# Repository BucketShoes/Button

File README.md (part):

# Capture button

A capture point for LARP battle games, made for [Battlecry LARP](https://battlecrylarp.org). Two teams fight
over a hand-sized button. To take it you hold its lid down for a few seconds, which is long enough
for an enemy nearby to hit you first. The button shows who owns it with a ring of team-coloured
lights, and can run a clock for each team, like a reverse chess clock: whoever owns it longest wins.

We used to mark points with scrunchies or flags on a pole, or with a chess clock, which needed a ref
standing next to it holding up a flag so players could see the score from a distance. The button lights
up for itself, and a capture takes a deliberate hold rather than the instant slap of a chess clock.

<p align="center"><a href="https://bucketshoes.github.io/Button/"><b>Open the control page</b></a>
&nbsp;·&nbsp; <a href="https://bucketshoes.github.io/Button/?demo"><b>Try the demo</b></a> (no hardware needed)</p>

The control page runs in Chrome on a phone and talks to the buttons over Bluetooth. From it a ref can see every
button at once, pause and resume the whole game, adjust clocks and change settings. The buttons work
fine without it. **The demo** runs five simulated buttons in your browser, with clocks ticking and captures happening
by themselves. Every control works on them, so open a button's settings and try things out.

| | |
|---|---|
|  |  |
| Assembled, lid on (displays off) | Board, lid and shell as delivered by JLCPCB / JLC3DP |
|  |  |
| The b43 board (KiCad) | Case section: lid, return spring and pushers over the shell |

Photos of it powered on don't come out: the displays and charge LED blow out, so the photos above show it off.

## What's in it

- **ESP32-C6** module, two 4-digit 7-segment displays (one per team), 8 WS2812 LEDs in a ring,
  three switches under the lid, a speaker, USB-C charging and an 18650 cell.
- A **3D-printed case**: a translucent lid that presses the switches through printed pushers, over a shell
  that holds the board with a twist-lock. The shell is JLC3DP's 9600 white resin, thin enough that the
  LEDs glow out through its sides. The lid is 8001 clear resin: without any smoothing treatment it's a little
  diffuse, but the large displays read easily through it.
- **Firmware** in C on ESP-IDF, with a Bluetooth LE protocol for the control page.

## What's in this repo

| Where | What |
|---|---|
| [`src/`](src) | Firmware (ESP-IDF via PlatformIO): see [Building the firmware](#building-the-firmware) |
| [`docs/index.html`](docs/index.html) | The control page, served by GitHub Pages ([`demo.js`](docs/demo.js) is its demo mode; [`sw.js`](docs/sw.js) and the manifest make it installable and usable offline) |
| [`docs/ble-protocol.md`](docs/ble-protocol.md) | The Bluetooth protocol, if you want to write your own controller |
| [`docs/hardware.md`](docs/hardware.md) | Pin map, power, displays, LEDs and audio, as built on board b43 |
| [`docs/design-notes.md`](docs/design-notes.md), [`docs/plans.md`](docs/plans.md) | Design notes, game ideas, and what's planned |
| [`pcb/`](pcb) | KiCad 10 project for board b43, and the JLC production files |
| [`case/`](case) | Case STEP (lid, shell and sleeve, v43) as sent to JLC3DP |
| [`docs/next-revision.md`](docs/next-revision.md) | **Read this before building your own:** what we'd change after the first boards and cases arrived, and the cost |

## Building one

Everything was ordered from JLC: the board assembled by JLCPCB, and the case printed in resin by JLC3DP.

- **Every assembled part has an LCSC part number** in the board file (`LCSC Part #`), so the BOM and placement files
  in [`pcb/production b43.zip`](pcb) go straight into a JLCPCB assembly order. They're mostly basic and
  promotional parts, so the extended-part fees stay low.
- **Some soldering is still needed.** JLC wouldn't place the 8 WS2812B LEDs: they're moisture class MSL 5a,
  even though they're listed as available for economic assembly. The 18650 holder on the back and any external
  wires (speaker, pedals, LED strip) are also hand-soldered.
- **A pouch cell instead of the 18650** works fine, but connect it through a plug (JBAT1 takes a 2-pin PH 2.0
  connector) rather than soldering it straight on. The ESP is always powered from the cell, so a hard-wired cell
  leaves no way to power-cycle a stuck button.
- **Order the case** from [`case/larp-v43 print.step`](case): the shell (and sleeve) in 9600 white resin, the lid in 8001 clear resin, untreated.
- **Flash the firmware** over USB-C (see below), then connect from the control page.
- **Before ordering**, read [`docs/next-revision.md`](docs/next-revision.md): the first articles showed fit,
  spring and rattle problems in the case, and a few board changes.

### Opening the board in KiCad

[`pcb/`](pcb) has the schematic, board, project libraries (`LARP.kicad_sym`, `LARP.pretty`), design rules and
Fabrication Toolkit settings. It needs KiCad 10.

- **3D models:** the EasyEDA/LCSC models aren't in the repo, because their redistribution terms are unclear. Fetch them with:

  ```
  pip install easyeda2kicad
  python tools/fetch_3d_models.py
  ```

  The script puts each model where the board expects it, and checks it against [`pcb/models.sha256`](pcb/models.sha256), the exact files
  the board was designed with. The board file and gerbers don't depend on them; only the 3D view does.
- **Schematic:** it matches the b43 board, except that USBC1 uses a different 16-pin USB-C footprint on the board.
  The mounting holes and a net tie are on the board only.
- **How the files were made:** scripts generated the KiCad files with the parts and nets but no layout. The
  layout was then done by hand in KiCad, and later tweaks were a mix of KiCad edits and direct edits to the files,
  so the files here, not the scripts, are the source.

## Licence

- **Firmware, control page and tools:** [GPL-3.0-or-later](LICENSE).
- **Hardware (`pcb/`, `case/`) and documentation:** [CC BY-SA 4.0](LICENSE-hardware.md).

## Building the firmware

The firmware is C on **ESP-IDF 5.5.1**, built with [PlatformIO](https://platformio.org) (the pioarduino platform 55.03.31,
which brings its own ESP-IDF; nothing else to install).

1. Install VS Code and its PlatformIO extension, then open this folder. The first build downloads the toolchain,
   which takes a few minutes.
2. Plug the board in by USB-C and pick its port in the status bar.
3. Run the PlatformIO **Upload** task. The ESP32-C6's native USB usually just works, but not on every module. If it won't
   connect, or keeps dropping out, power it fully down first: take out the 18650, or unplug the pouch cell. Then hold
   BOOT (inside the case) while plugging in USB, and upload. That keeps the chip in its bootloader. On USB alone the
   power peaks at startup can reset the chip in a loop, and BOOT stops the loop long enough to flash.
4. Open the control page and connect. Settings (name, mode, durations, colours and so on) are set from the page and
   saved on the button, so there's nothing to configure in the code.

From a terminal: `pio run -t upload --upload-port <port>`, then `pio device monitor --port <port>` for the serial log
(a status line every second and an event log). On Windows `pio` usually isn't on PATH; it's
`~\.platformio\penv\Scripts\pio.exe`.

Chip options are in `sdkconfig.defaults`; delete the generated `sdkconfig.button` after editing it.
The flash layout is in `partitions.csv`: a 3 MB app and a 4 MB `audio` partition.

<details>
<summary>Optional: a music clip</summary>

The `audio` partition can hold a clip of about 40 s, played from the page with the "Music clip" sound. It was added as a
speaker test, and the button works fine without it. Upload leaves it alone unless `custom_audio` in `platformio.ini` says otherwise:
`upload` also writes `audio/test_audio.bin`, and `erase` blanks it. Set it back to `keep` afterwards, because the clip makes uploads slow.

To make the clip from any MP3 (`transcode.ps1` uses Windows' own decoder, so no ffmpeg is needed):

```
powershell -File tools	ranscode.ps1 -Src "song.mp3" -OutDir <dir> -OutName music.wav
python tools\make_test_audio.py <dir>\music.wav audio	est_audio.bin
```

`make_test_audio.py` takes the first 40 s and normalises the level (see `--help` for the start point, high-pass and
compression). It also writes `audio/test_audio.wav`, the exact samples the button plays, for listening on a PC.
The format is raw 16-bit mono PCM at 48 kHz with a 16-byte header.
</details>

## Control page (Web Bluetooth)

[docs/index.html](docs/index.html) is published by GitHub Pages at
<https://bucketshoes.github.io/Button/>. Open it in Chrome (Android, or Chrome/Edge on a computer) and
press **Connect a button**. You can connect several buttons. With no hardware, add `?demo` to the address for five simulated buttons
(<https://bucketshoes.github.io/Button/?demo>).

- **Install it as an app** (optional): use the **Install as an app** link at the bottom of the page, or Chrome's menu
  (**Add to Home screen** on Android, **Install** on a computer). The page doesn't pop up an install offer by itself.
  It then opens full-screen from its own icon. Installed or not, it also works with no internet once it has been opened
  once, which helps at game sites with no reception. With a connection it always loads the newest version.
- **iPhone:** no iPhone browser has Web Bluetooth (they're all Safari underneath, including Chrome), so the page
  can't connect, installed or not. A Web Bluetooth browser app such as Bluefy may work; it hasn't been tested.

- **Keep screen on** (at the bottom of the page, on by default): stops the phone locking while the page is in front, so a ref can glance at it mid-game. Chrome allows it straight away; a browser that wants a tap first gets one from the next tap anywhere on the page. Next to it, "(on)" means it is working. Untick it to save battery; the choice is remembered.
- **Game bar** (top): pause and resume the whole game, and play a sound (whistle by default) on every button. Game resume undoes the game pause: each button goes back to exactly what it was doing, so a button that was paused or uncaptured stays that way.
- **Overview:** one row per button, sized so about 5 fit on a phone screen. Name and battery on the left, then a box per team (team names once at the top of each column):
  - thick border in the team colour, filled for the owner;
  - underlined time while that clock is ticking, blinking on a win. In one-timer mode the shared clock shows in the owner's box only, and the other box is empty;
  - a small pie fills while someone holds the lid, in the box of the team about to capture;
  - tap a row to jump to that button's panel.
- **Each button** gets its own panel below:

- **Controls:** start, pause, reset, identify (displays and ring flash with beeps for 3 s), battery, and power off.
- **Owner:** set the owner (uncaptured / team 1 / team 2).
- **Reboot** (in settings), for when something is stuck. Settings are kept; the game state is lost.
- **Sounds:** play any of the button's sounds, or stop them.
- **Clocks:** live clocks (one shared clock in one-timer mode), −1 min / −10 s, +1 min / +10 s, or set an exact time (m:ss), even while running.
- **Settings (saved on the button):**
  - name and mode (teams only / one timer / two timers);
  - count down or up, and whether the numbers show on the displays;
  - durations (one in one-timer mode), the owner after reset, the first capture (random / team 1 / team 2), the hold time, the team colours, the volume and the LED brightness;
  - "Copy to all" sends the settings to every connected button, keeping each name.
- **More for all buttons** (under the overview): identify, power on and power off all of them at once.
- **Reboots:** the panel shows how many times the button restarted since power-on, why it last did (for example brown-out) and how long ago. Wakes from deep sleep (shipping, low battery) don't count. The count is kept in RTC RAM: a reset, a reflash or a brown-out keeps it; only losing all power (the cell and USB both gone) clears it.
- **Wall clock** with seconds in the top corner.

The protocol is in [docs/ble-protocol.md](docs/ble-protocol.md).

## Behaviour

- **Modes:**
  - **Teams only:** the ring shows who owns the button. There are no clocks: the owner's display shows dashes ("--:--") with the same colon, highlight and hold cues as a clock, and the other display is blank.
  - **One timer:** one shared clock, which runs whichever team owns the button. Whoever owns it when the clock runs out wins. It shows only on the owner's display, and the other display is blank, so it reads as one clock that belongs to them. While uncaptured it shows on one display only, neither lit: the team the next press goes for (the first display when that's random).
  - **Two timers:** a reverse chess clock; the owner's clock runs.
  - **"Own" and "hold":** a team *owns* the button (it's in their control); a player *holds* the lid (pressing it).
- **Clocks:** count down (win at 0:00) or up (win at the duration; a duration of 0 means no limit). Default: two timers counting down from 10:00.
- **Face press:** any of the three switches counts (an OR). The lid counts as pressed until 50 ms after the last contact.
- **Hold**, where H is the hold time (default 3 s):
  - **Up to H:** the ring shows the team about to capture. The first LED is lit at once, and the others wait dim, at the lowest brightness setting. Each comes on in turn with a short smooth fade (0.2 s) at the end of its fifth of the hold, so it's a clear step around the ring, and the capture happens as the 6th comes on. While it builds, the lit LEDs are at least 16 % (8 times the dim ones, so they're clearly apart at any setting) and the team LEDs light as bright as the ring; it goes back to the set brightness once captured. The build-up sound is made for the hold time, so it lasts exactly until the capture: a rising whoop (sci-fi), or drums accelerating under a climbing horn, ending in a snare roll (medieval). Letting go early puts it back as it was.
  - **At H, capture:** while running it goes to the other team; while paused it resumes with the same team. The ring and displays go dark for 0.1 s, as a "done", then show the new owner as normal while its call plays out. The count towards the pause starts only once the call has finished, at C (H plus the longer of the two teams' calls, so it's the same whichever team captured: about 0.65 s in sci-fi, 1.5 s in medieval), so the call isn't talked over and the next thing is clearly something else.
  - **Uncaptured:** the team is decided the moment the hold starts and shows straight away: the ring fills in its colour and its display lights. Wrong colour? Let go and press again: every press that doesn't capture flips the team for the next press. The first press uses the "first capture" setting, which is random by default.
  - **C to C+4 s:** the ring fills white with a ding each second, then a **pause** at C+4 s (about 8 s with the default hold). The clocks go back to where they were before the hold, and the paused owner is:
    - **was running:** whoever had it before the hold;
    - **was uncaptured:** the team just picked, so a hold to the pause pre-sets the owner at 10:00 (for example at a respawn);
    - **was paused:** the same team: the hold is undone.
  - **C+4 to C+9 s:** doom each second, then a **reset** at C+9 s (about 13 s).
  - **C+9 to C+14 s:** after a second, the displays say "HoLd" "oFF" with a falling tone and the ring drains; at C+14 s (about 18 s) it **powers off**. Let go before that and it stays on, just reset.
  - **During a game pause** (from the page): a press plays the pause sound and nothing is captured, so a player who hasn't noticed can't change anything. The ring fills slowly white; at H+4 s the button leaves the game pause into a regular pause, owner and clocks unchanged, and works normally from then on (so the page is never required). H+9 s still resets. (Nothing is captured, so there is no call to wait for: C is H here, and after a win.)
  - **After a win**, the fanfare repeats for 20 s. Holding dings every second all the way to the reset (there is no pause to warn about): H silences the fanfare, and H+9 s resets.
- **Idle cues:**
  - **Not held, the button shows only the true state.** A hold let go early snaps straight back, so nobody runs off thinking they captured it.
  - **Uncaptured:** a faint white pulse on the ring (0–10 %, 0.5 Hz), no team colour, and neither display highlighted. The team the next press goes for has one colon dot missing: subtle, for admins.
  - **Paused with an owner:** the ring blinks faintly in their colour, and their display shows a single slow-blinking dot instead of the colon.
- **After reset:** uncaptured, or owned by the team set in "after reset". In teams-only mode that team is simply live. With clocks it waits, paused, for Start or a hold.
- **Lines** (tug-of-war, forge-a-path; set up in the page's "Lines" (changes go to the buttons on Save), or by holding several buttons to the reset at once; default settings take a button out of its line):
  - A team can take a button only next to one it owns, or at its end of the line (each end's team, or none, is a setting). Forge-a-path: a button once taken stays taken.
  - Retake (a button just taken can't be taken back) and advance (a button just opened by its neighbour's capture can't be taken yet) are 0 s and 20 s by default (0 is allowed for either), counted on the network clock. An owner an admin sets is open at once (no count); saving a line's settings keeps any count that's running. A press on a paused button goes to its own owner, a resume, which is always allowed.
  - **Displays:** nobody can take it: "--:--" on both, dim. Counting down to when a team can: the time on that team's display, the rest as a teams-only button. Once it can be taken it's simply a teams-only button.
  - **Sounds:** a neighbour's capture that opens this button, or starts its count, plays a brief alert here ("dun dun" and a horn, or two beeps in sci-fi); the count running out plays a bell (or a blip).
  - **A press that isn't allowed:** a short low "no" and a red flash, and nothing builds up or captures. Not next to theirs: "nEEd" and the number of the button to take first, for 2 s. Holding on still pauses and resets as usual.
  - **Forming without the page:** hold several buttons at once (a stack, pressed together) until the reset. From the pause on they flash one shared colour together; at the reset they become a line, numbered in node-id order, the first half team 1, the rest team 2 (a middle one either), and show "LinE" and their place ("4  3": line 4, 3rd; lines are numbered 1–6, each with its own colour, and a new one avoids the numbers in use) for 20 s, with a sweep down the line in its colour. A button held to the reset alone leaves its line. A reset in a line goes back to the team the line gave it; the button's own "after reset" setting is kept for when it leaves. The line is kept in flash, so a button that restarts is still in it. In a line a button is in teams-only mode; leaving puts its own mode back.
  - **Four taps:** "LinE" and its place again for 2 s ("--" when not in a line); on joining it shows for 15 s.
- **Triple tap:** battery ("bAtt" plus a percent for 2 s, with a green gauge on the ring). It works in every mode and with the numbers hidden. The latest tap code is what shows; 1, 2 or 5 or more taps put the display back to normal.
- **Power:** see "Power" below.
- **BOOT:**
  - Hold: the displays say "HoLd" "oFF" with a falling tone, and at 3 s it **powers off** (no need to let go).
  - Keep holding to 8 s: restore the default settings (it wakes briefly to play the sound).
  - A press while the music clip plays only stops the clip.
- **Volume** defaults to 80 % and **LEDs** to 50 %. Volume is in even dB steps (0.4 dB a percent, 100 % = full scale) and goes on to 125 % (+10 dB): past 100 the loudest peaks go into a soft knee above −2 dBFS. Full volume can brown out on USB-only power. The brightness setting dims the displays too. In the medieval set the plain beeps (admin sounds) play 6 dB lower, to sit with the instruments.
- **Brown-out recovery:**
  - The game carries on. The game state is copied to RTC RAM all the time, and a brown-out reset leaves that RAM and the low-power timer running. After a brown-out, crash or watchdog reset, the button comes back with the same owner, clocks and running/paused state, with the clock advanced by the second or so it spent rebooting. A button that was off comes back off. If the RAM didn't survive (the checksum fails), or the power was really lost, it starts fresh as after a reset. A reboot from the page also starts fresh.
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
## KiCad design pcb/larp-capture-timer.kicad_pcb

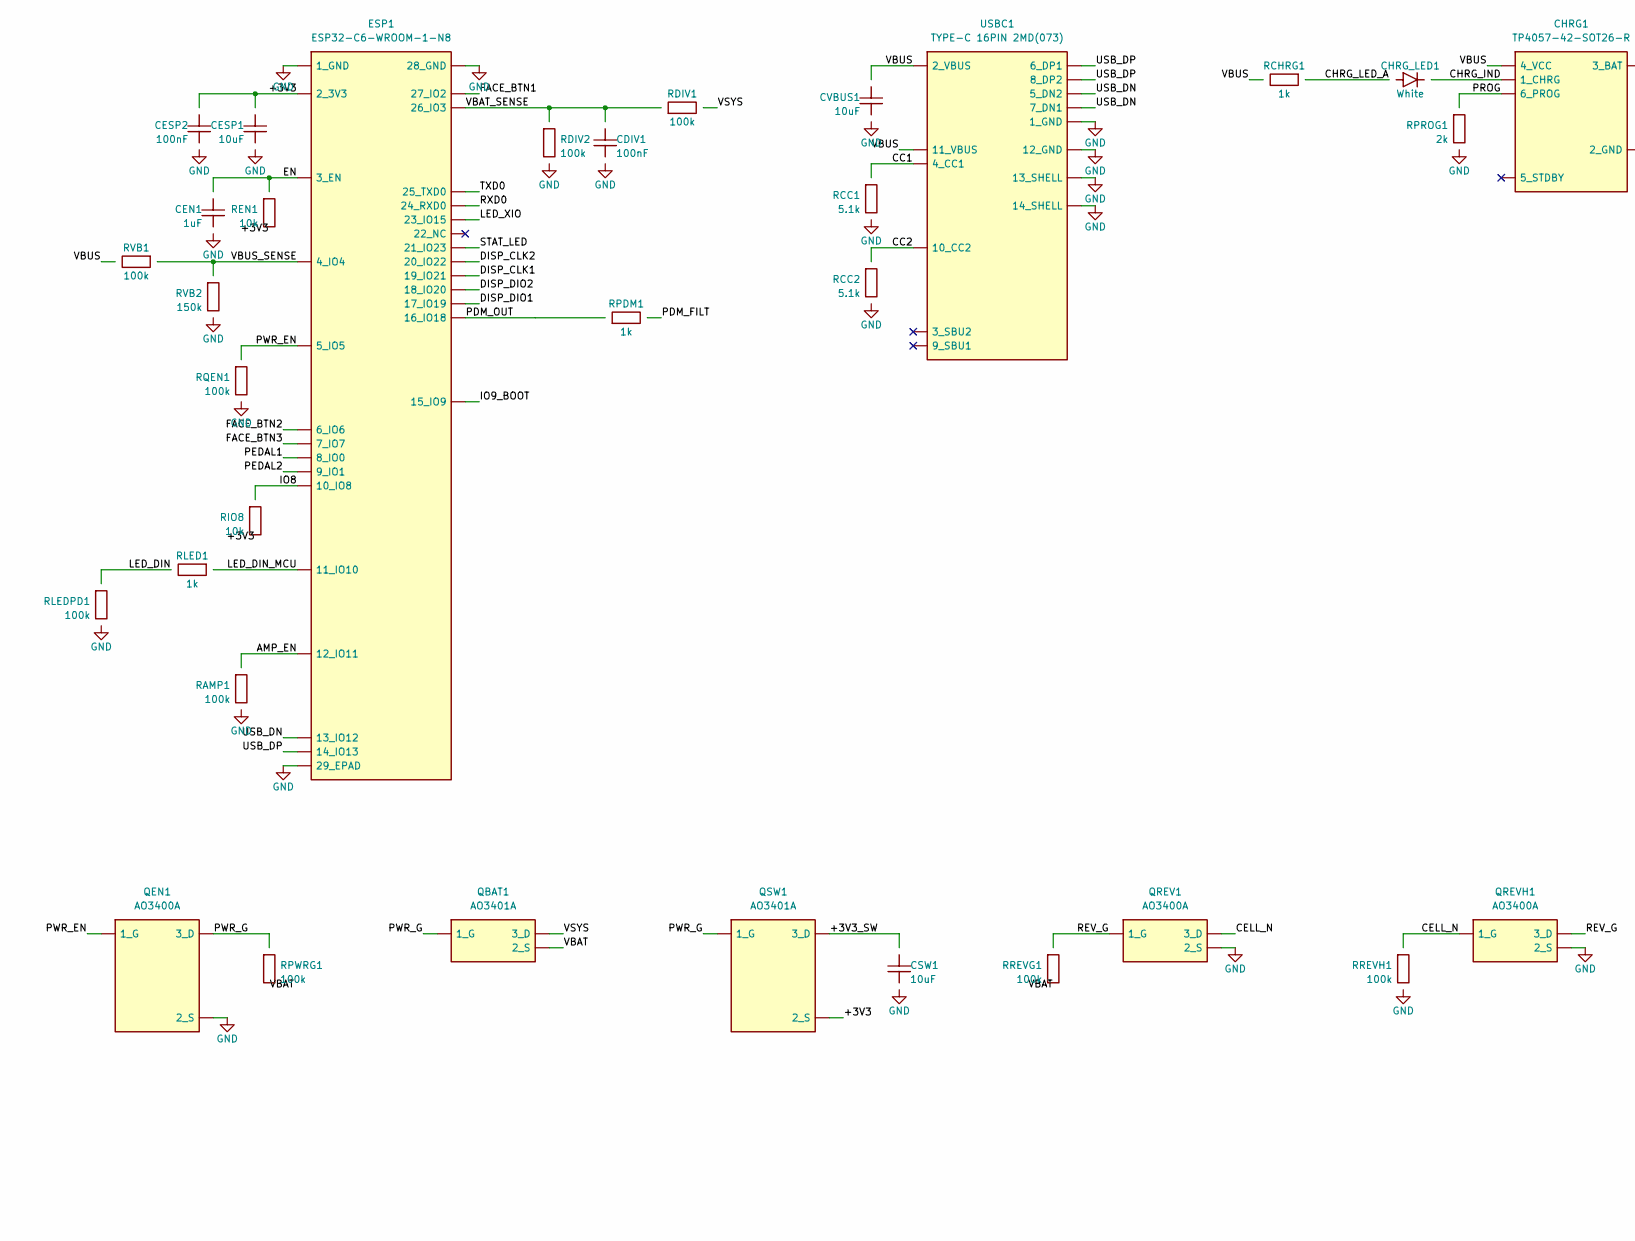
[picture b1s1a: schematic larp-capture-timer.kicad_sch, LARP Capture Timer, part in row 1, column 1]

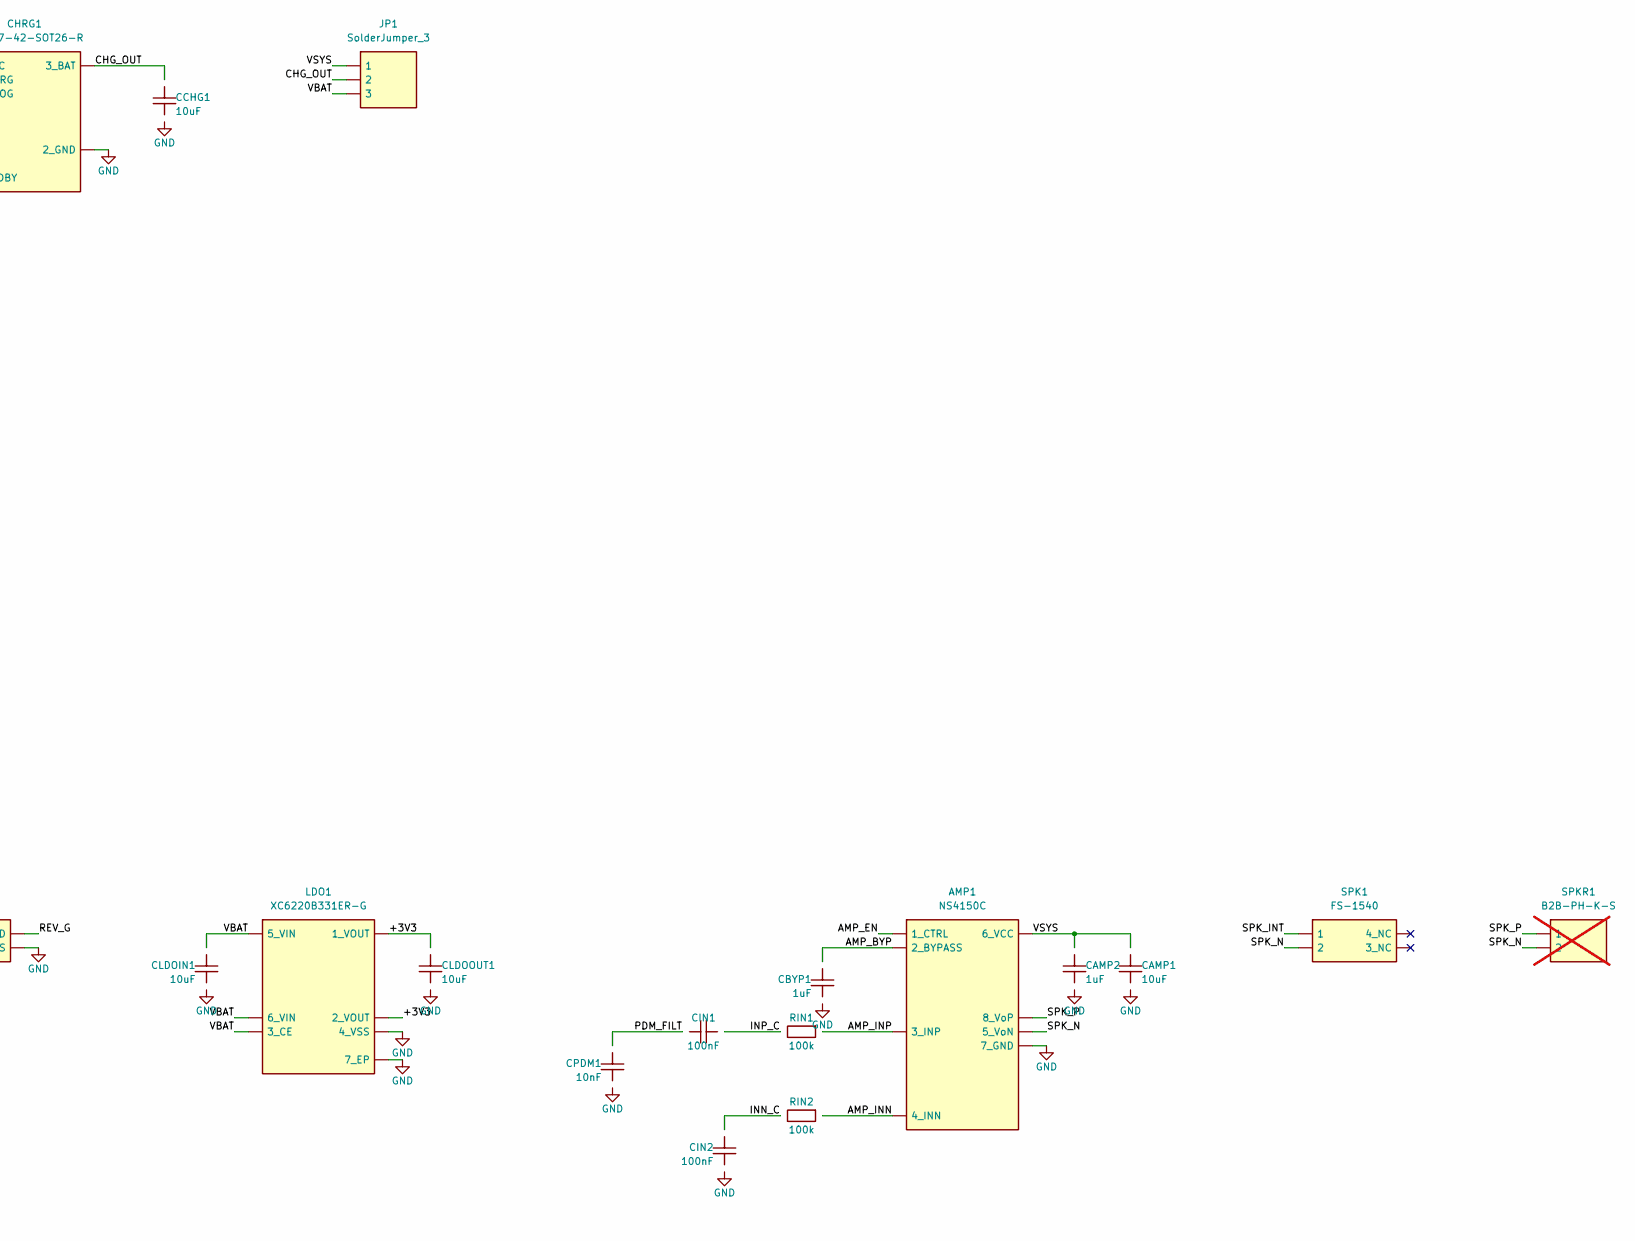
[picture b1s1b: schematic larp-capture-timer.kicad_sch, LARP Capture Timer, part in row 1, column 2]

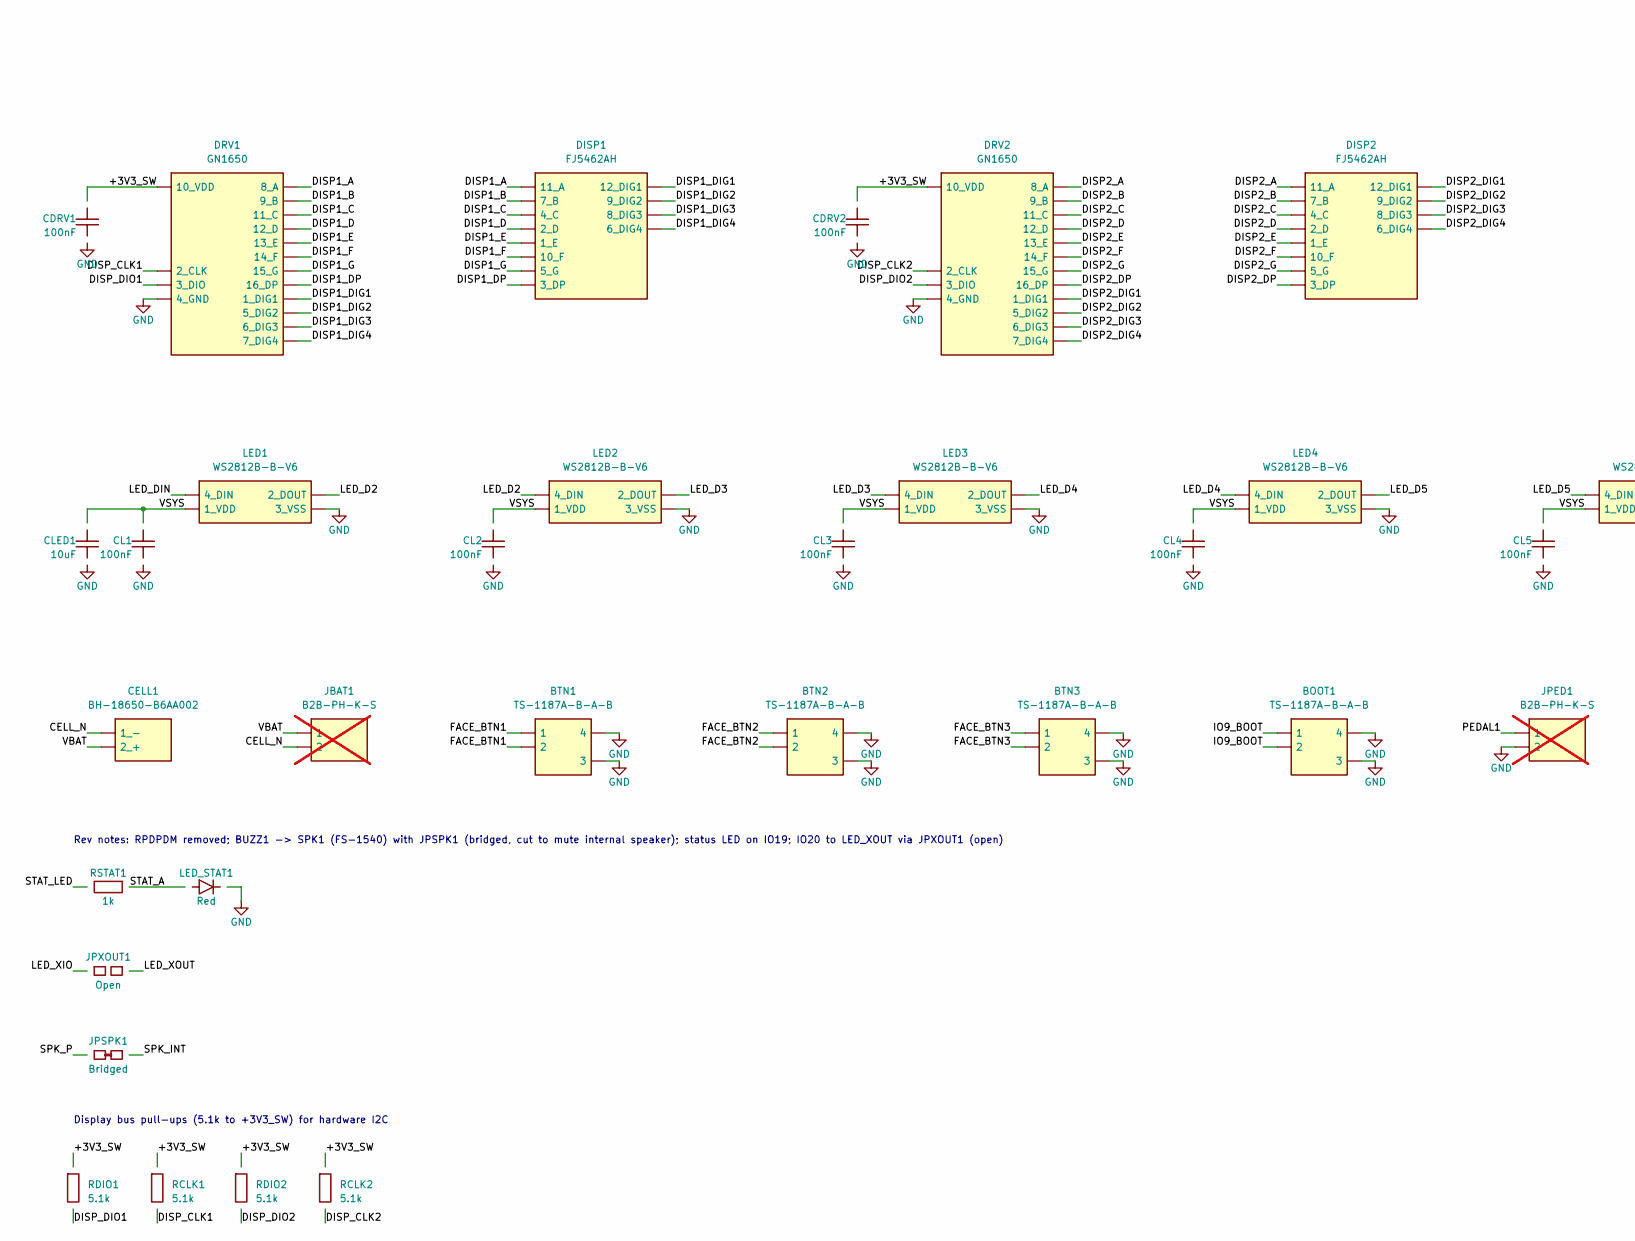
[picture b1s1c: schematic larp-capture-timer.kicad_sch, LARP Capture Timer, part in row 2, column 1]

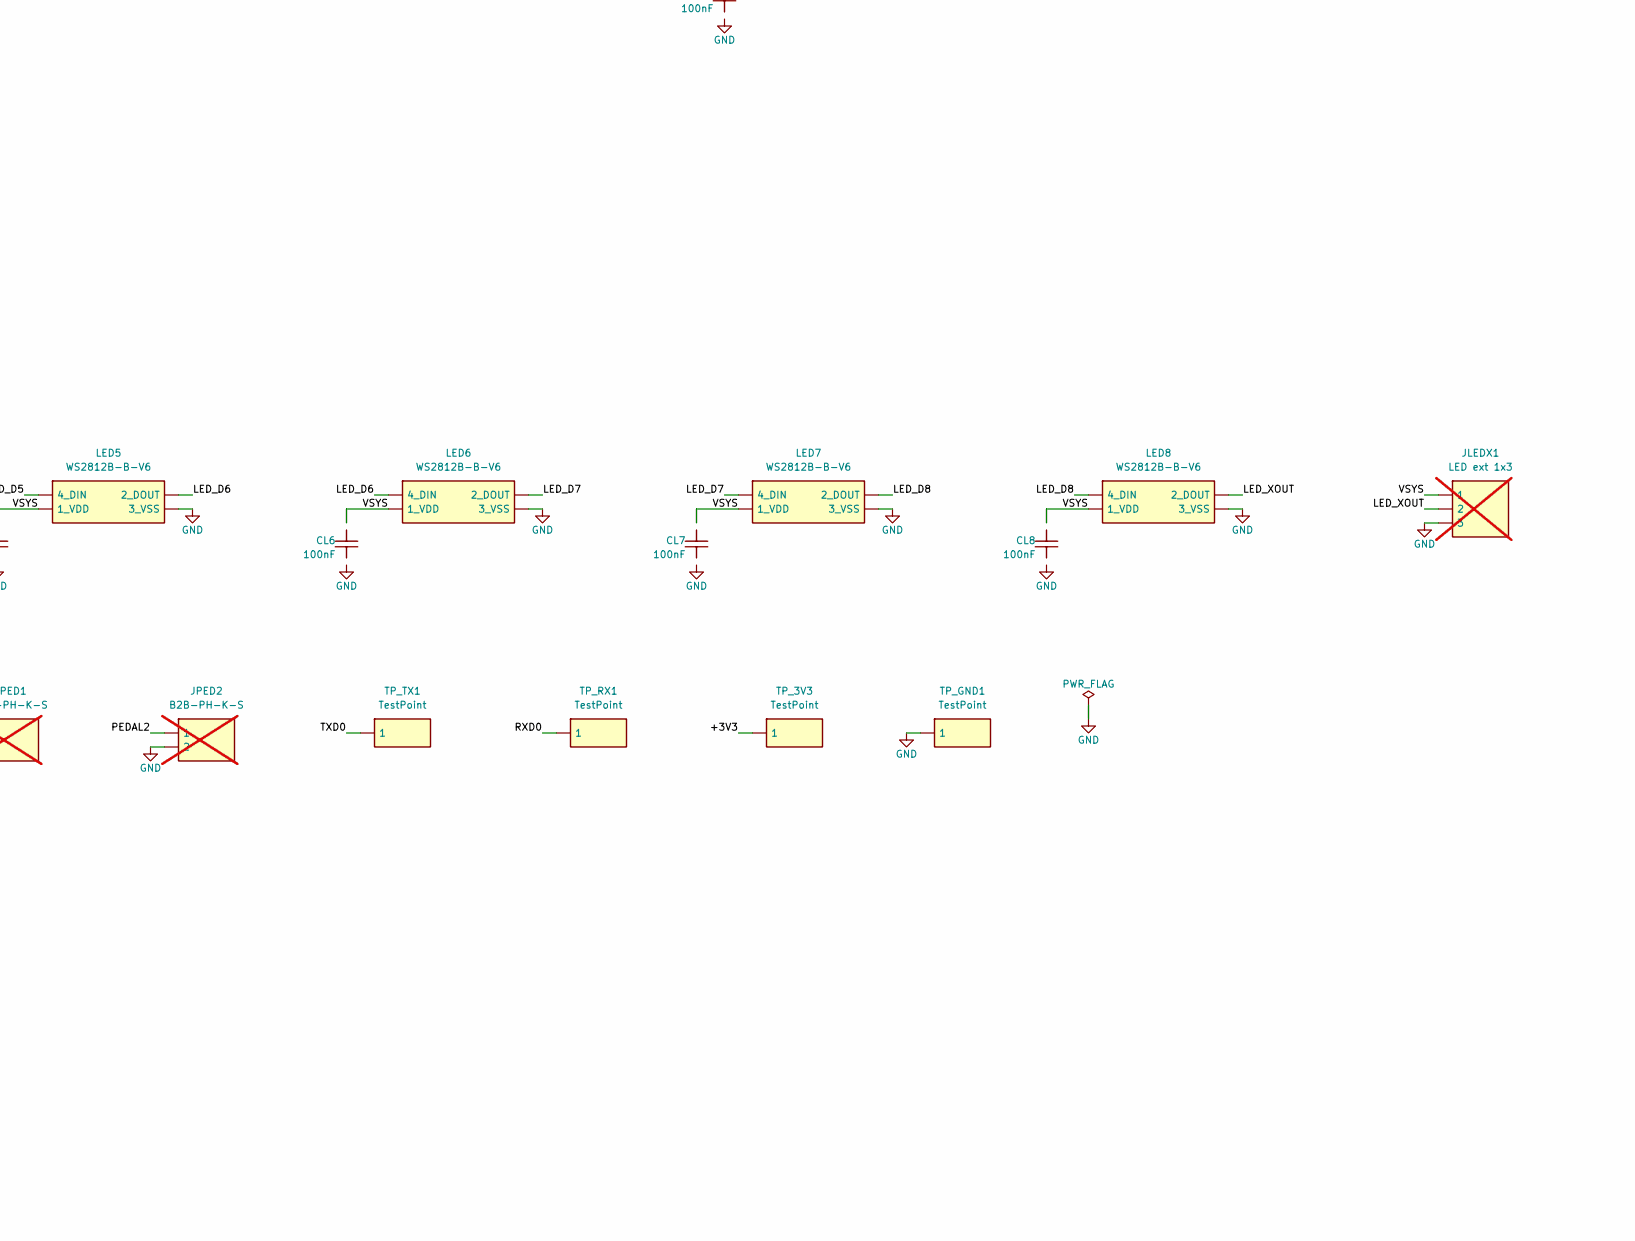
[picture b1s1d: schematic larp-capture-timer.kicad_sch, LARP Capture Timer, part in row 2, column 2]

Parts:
AMP1: NS4150C; SOP-8_L4.9-W3.9-P1.27-LS6.0-BL_NS4150C; LCSC Part # C2875838
BOOT1: TS-1187A-B-A-B; SW-SMD_4P-L5.1-W5.1-P3.70-LS6.5-TL_H1.5; LCSC Part # C318884
BTN1, BTN2, BTN3: TS-1187A-B-A-B; SW-SMD_4P-L5.1-W5.1-P3.70-LS6.5-TL_H1.5; LCSC Part # C318884
CAMP1: 10uF; C_0603_1608Metric; LCSC Part # C19702
CAMP2: 1uF; C_0603_1608Metric; LCSC Part # C15849
CBYP1: 1uF; C_0603_1608Metric; LCSC Part # C15849
CCHG1: 10uF; C_0603_1608Metric; LCSC Part # C19702
CDIV1: 100nF; C_0603_1608Metric; LCSC Part # C14663
CDRV1, CDRV2: 100nF; C_0603_1608Metric; LCSC Part # C14663
CELL1: BH-18650-B6AA002; BATTERY-SMD_18650-1S-L77.1-W20.7-1; LCSC Part # C7525438
CEN1: 1uF; C_0603_1608Metric; LCSC Part # C15849
CESP1: 10uF; C_0603_1608Metric; LCSC Part # C19702
CESP2: 100nF; C_0603_1608Metric; LCSC Part # C14663
CHRG1: TP4057-42-SOT26-R; SOT-23-6_L2.9-W1.6-P0.95-LS2.8-BL_TP4057-42-SOT26-R; LCSC Part # C12044
CHRG_LED1: White; LED_0603_KA; LCSC Part # C2290
CIN1, CIN2: 100nF; C_0603_1608Metric; LCSC Part # C14663
CL1, CL2, CL3, CL4, CL5, CL6, CL7, CL8: 100nF; C_0603_1608Metric; LCSC Part # C14663
CLDOIN1: 10uF; C_0603_1608Metric; LCSC Part # C19702
CLDOOUT1: 10uF; C_0603_1608Metric; LCSC Part # C19702
CLED1: 10uF; C_0603_1608Metric; LCSC Part # C19702
CPDM1: 10nF; C_0603_1608Metric; LCSC Part # C57112
CSW1: 10uF; C_0603_1608Metric; LCSC Part # C19702
CVBUS1: 10uF; C_0603_1608Metric; LCSC Part # C19702
DISP1, DISP2: FJ5462AH; LED-SEG-TH_12P-L50.3-W19.0-P2.54-S15.24-BL_FJ5462AH; LCSC Part # C46908
DRV1, DRV2: GN1650; SOP-16_L9.9-W3.9-P1.27-LS6.1-BL_GN1650; LCSC Part # C427456
ESP1: ESP32-C6-WROOM-1-N8; ESP32-C6-WROOM-1; LCSC Part # C5366877
JBAT1: B2B-PH-K-S; CONN-TH_B2B-PH-K-S; LCSC Part # C131337; not fitted
JLEDX1: LED ext 1x3; HDR-TH_3P-P2.54-V-M_PZ254V-11-03P; LCSC Part # C2937625; not fitted
JP1: SolderJumper_3; SolderJumper-3_P1.3mm_Open_Pad1.0x1.5mm
JPED1, JPED2: B2B-PH-K-S; CONN-TH_B2B-PH-K-S; LCSC Part # C131337; not fitted
JPSPK1: Bridged; SolderJumper-2_P1.3mm_Bridged_RoundedPad1.0x1.5mm
JPXOUT1: Open; SolderJumper-2_P1.3mm_Open_RoundedPad1.0x1.5mm
LDO1: XC6220B331ER-G; USP-6C_L2.0-W1.8-P0.50-BL-EP_XC6220B331ER-G; LCSC Part # C3013657
LED1, LED2, LED3, LED4, LED5, LED6, LED7, LED8: WS2812B-B-V6; LED-SMD_4P-L5.0-W5.0-TL_WS2812B-B_WS2812B-B-V6; LCSC Part # C52941391
LED_STAT1: Red; LED_0603_KA; LCSC Part # C2286
QBAT1: AO3401A; SOT-23_L2.9-W1.3-P1.90-LS2.4-BR_AO3401A; LCSC Part # C15127
QEN1: AO3400A; SOT-23-3_L2.9-W1.3-P1.90-LS2.4-BR_AO3400A; LCSC Part # C20917
QREV1: AO3400A; SOT-23-3_L2.9-W1.3-P1.90-LS2.4-BR_AO3400A; LCSC Part # C20917
QREVH1: AO3400A; SOT-23-3_L2.9-W1.3-P1.90-LS2.4-BR_AO3400A; LCSC Part # C20917
QSW1: AO3401A; SOT-23_L2.9-W1.3-P1.90-LS2.4-BR_AO3401A; LCSC Part # C15127
RAMP1: 100k; R_0603_1608Metric; LCSC Part # C25803
RCC1, RCC2: 5.1k; R_0603_1608Metric; LCSC Part # C23186
RCHRG1: 1k; R_0603_1608Metric; LCSC Part # C21190
RCLK1, RCLK2: 5.1k; R_0603_1608Metric; LCSC Part # C23186
RDIO1, RDIO2: 5.1k; R_0603_1608Metric; LCSC Part # C23186
RDIV1, RDIV2: 100k; R_0603_1608Metric; LCSC Part # C25803
REN1: 10k; R_0603_1608Metric; LCSC Part # C25804
RIN1, RIN2: 100k; R_0603_1608Metric; LCSC Part # C25803
RIO8: 10k; R_0603_1608Metric; LCSC Part # C25804
RLED1: 1k; R_0603_1608Metric; LCSC Part # C21190
RLEDPD1: 100k; R_0603_1608Metric; LCSC Part # C25803
RPDM1: 1k; R_0603_1608Metric; LCSC Part # C21190
RPROG1: 2k; R_0603_1608Metric; LCSC Part # C22975
RPWRG1: 100k; R_0603_1608Metric; LCSC Part # C25803
RQEN1: 100k; R_0603_1608Metric; LCSC Part # C25803
RREVG1: 100k; R_0603_1608Metric; LCSC Part # C25803
RREVH1: 100k; R_0603_1608Metric; LCSC Part # C25803
RSTAT1: 1k; R_0603_1608Metric; LCSC Part # C21190
RVB1: 100k; R_0603_1608Metric; LCSC Part # C25803
RVB2: 150k; R_0603_1608Metric; LCSC Part # C22807
SPK1: FS-1540; SPK-SMD_FS-1540; LCSC Part # C482341
SPKR1: B2B-PH-K-S; CONN-TH_B2B-PH-K-S; LCSC Part # C131337; not fitted
TP_3V3: TestPoint; TestPoint_Pad_D1.0mm
TP_GND1: TestPoint; TestPoint_Pad_D1.0mm
TP_RX1: TestPoint; TestPoint_Pad_D1.0mm
TP_TX1: TestPoint; TestPoint_Pad_D1.0mm
USBC1: TYPE-C 16PIN 2MD(073); USB-C-SMD_TYPE-C-16PIN-2MD-073_TYPE-C16PIN2MD073; LCSC Part # C2765186

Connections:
/+3V3: CESP1.1, CESP2.1, CLDOOUT1.1, ESP1.2_3V3, LDO1.1_VOUT, LDO1.2_VOUT, QSW1.2_S, REN1.2, RIO8.2, TP_3V3.1 (1_1)
/+3V3_SW: CDRV1.1, CDRV2.1, CSW1.1, DRV1.10_VDD, DRV2.10_VDD, QSW1.3_D, RCLK1.1, RCLK2.1, RDIO1.1, RDIO2.1
/AMP_BYP: AMP1.2_BYPASS, CBYP1.1
/AMP_EN: AMP1.1_CTRL, ESP1.12_IO11, RAMP1.1
/AMP_INN: AMP1.4_INN, RIN2.1
/AMP_INP: AMP1.3_INP, RIN1.1
/CC1: RCC1.1, USBC1.4_CC1
/CC2: RCC2.1, USBC1.10_CC2
/CELL_N: CELL1.1_-, JBAT1.2, QREV1.3_D, QREVH1.1_G, RREVH1.1
/CHG_OUT: CCHG1.1, CHRG1.3_BAT, JP1.2
/CHRG_IND: CHRG1.1_CHRG, CHRG_LED1.1_K
/CHRG_LED_A: CHRG_LED1.2_A, RCHRG1.1
/DISP1_A: DISP1.11_A, DRV1.8_A
/DISP1_B: DISP1.7_B, DRV1.9_B
/DISP1_C: DISP1.4_C, DRV1.11_C
/DISP1_D: DISP1.2_D, DRV1.12_D
/DISP1_DIG1: DISP1.12_DIG1, DRV1.1_DIG1
/DISP1_DIG2: DISP1.9_DIG2, DRV1.5_DIG2
/DISP1_DIG3: DISP1.8_DIG3, DRV1.6_DIG3
/DISP1_DIG4: DISP1.6_DIG4, DRV1.7_DIG4
/DISP1_DP: DISP1.3_DP, DRV1.16_DP
/DISP1_E: DISP1.1_E, DRV1.13_E
/DISP1_F: DISP1.10_F, DRV1.14_F
/DISP1_G: DISP1.5_G, DRV1.15_G
/DISP2_A: DISP2.11_A, DRV2.8_A
/DISP2_B: DISP2.7_B, DRV2.9_B
/DISP2_C: DISP2.4_C, DRV2.11_C
/DISP2_D: DISP2.2_D, DRV2.12_D
/DISP2_DIG1: DISP2.12_DIG1, DRV2.1_DIG1
/DISP2_DIG2: DISP2.9_DIG2, DRV2.5_DIG2
/DISP2_DIG3: DISP2.8_DIG3, DRV2.6_DIG3
/DISP2_DIG4: DISP2.6_DIG4, DRV2.7_DIG4
/DISP2_DP: DISP2.3_DP, DRV2.16_DP
/DISP2_E: DISP2.1_E, DRV2.13_E
/DISP2_F: DISP2.10_F, DRV2.14_F
/DISP2_G: DISP2.5_G, DRV2.15_G
/DISP_CLK1: DRV1.2_CLK, ESP1.19_IO21, RCLK1.2
/DISP_CLK2: DRV2.2_CLK, ESP1.20_IO22, RCLK2.2
/DISP_DIO1: DRV1.3_DIO, ESP1.17_IO19, RDIO1.2
/DISP_DIO2: DRV2.3_DIO, ESP1.18_IO20, RDIO2.2
/EN: CEN1.1, ESP1.3_EN, REN1.1
/FACE_BTN1: BTN1.1, BTN1.2, ESP1.27_IO2
/FACE_BTN2: BTN2.1, BTN2.2, ESP1.6_IO6
/FACE_BTN3: BTN3.1, BTN3.2, ESP1.7_IO7
/INN_C: CIN2.1, RIN2.2
/INP_C: CIN1.1, RIN1.2
/IO8: ESP1.10_IO8, RIO8.1
/IO9_BOOT: BOOT1.1, BOOT1.2, ESP1.15_IO9
/LED_D2: LED1.2_DOUT, LED2.4_DIN
/LED_D3: LED2.2_DOUT, LED3.4_DIN
/LED_D4: LED3.2_DOUT, LED4.4_DIN
/LED_D5: LED4.2_DOUT, LED5.4_DIN
/LED_D6: LED5.2_DOUT, LED6.4_DIN
/LED_D7: LED6.2_DOUT, LED7.4_DIN
/LED_D8: LED7.2_DOUT, LED8.4_DIN
/LED_DIN: LED1.4_DIN, RLED1.2, RLEDPD1.1
/LED_DIN_MCU: ESP1.11_IO10, RLED1.1
/LED_XIO: ESP1.23_IO15, JPXOUT1.2
/LED_XOUT: JLEDX1.2, JPXOUT1.1, LED8.2_DOUT
/PDM_FILT: CIN1.2, CPDM1.1, RPDM1.2
/PDM_OUT: ESP1.16_IO18, RPDM1.1
/PEDAL1: ESP1.8_IO0, JPED1.1
/PEDAL2: ESP1.9_IO1, JPED2.1
/PROG: CHRG1.6_PROG, RPROG1.1
/PWR_EN: ESP1.5_IO5, QEN1.1_G, RQEN1.1
/PWR_G: QBAT1.1_G, QEN1.3_D, QSW1.1_G, RPWRG1.1
/REV_G: QREV1.1_G, QREVH1.3_D, RREVG1.1
/RXD0: ESP1.24_RXD0, TP_RX1.1 (1_1)
/SPK_INT: JPSPK1.1, SPK1.1
/SPK_N: AMP1.5_VoN, SPK1.2, SPKR1.2
/SPK_P: AMP1.8_VoP, JPSPK1.2, SPKR1.1
/STAT_A: LED_STAT1.2_A, RSTAT1.1
/STAT_LED: ESP1.21_IO23, RSTAT1.2
/TXD0: ESP1.25_TXD0, TP_TX1.1 (1_1)
/USB_DN: ESP1.13_IO12, USBC1.5_DN2, USBC1.7_DN1
/USB_DP: ESP1.14_IO13, USBC1.6_DP1, USBC1.8_DP2
/VBAT: CELL1.2_+, CLDOIN1.1, JBAT1.1, JP1.3, LDO1.3_CE, LDO1.5_VIN, LDO1.6_VIN, QBAT1.2_S, RPWRG1.2, RREVG1.2
/VBAT_SENSE: CDIV1.1, ESP1.26_IO3, RDIV1.1, RDIV2.1
/VBUS: CHRG1.4_VCC, CVBUS1.1, RCHRG1.2, RVB1.2, USBC1.2_VBUS, USBC1.11_VBUS
/VBUS_SENSE: ESP1.4_IO4, RVB1.1, RVB2.1
/VSYS: AMP1.6_VCC, CAMP1.1, CAMP2.1, CL1.1, CL2.1, CL3.1, CL4.1, CL5.1, CL6.1, CL7.1, CL8.1, CLED1.1, JLEDX1.1, JP1.1, LED1.1_VDD, LED2.1_VDD, LED3.1_VDD, LED4.1_VDD, LED5.1_VDD, LED6.1_VDD, LED7.1_VDD, LED8.1_VDD, QBAT1.3_D, RDIV1.2
GND: AMP1.7_GND, BOOT1.3, BOOT1.4, BTN1.3, BTN1.4, BTN2.3, BTN2.4, BTN3.3, BTN3.4, CAMP1.2, CAMP2.2, CBYP1.2, CCHG1.2, CDIV1.2, CDRV1.2, CDRV2.2, CEN1.2, CESP1.2, CESP2.2, CHRG1.2_GND, CIN2.2, CL1.2, CL2.2, CL3.2, CL4.2, CL5.2, CL6.2, CL7.2, CL8.2, CLDOIN1.2, CLDOOUT1.2, CLED1.2, CPDM1.2, CSW1.2, CVBUS1.2, DRV1.4_GND, DRV2.4_GND, ESP1.1_GND, ESP1.28_GND, ESP1.29_EPAD, JLEDX1.3, JPED1.2, JPED2.2, LDO1.4_VSS, LDO1.7_EP, LED1.3_VSS, LED2.3_VSS, LED3.3_VSS, LED4.3_VSS, LED5.3_VSS, LED6.3_VSS, LED7.3_VSS, LED8.3_VSS, LED_STAT1.1_K, QEN1.2_S, QREV1.2_S, QREVH1.2_S, RAMP1.2, RCC1.2, RCC2.2, RDIV2.2, RLEDPD1.2, RPROG1.2, RQEN1.2, RREVH1.2, RVB2.2, TP_GND1.1 (1_1), USBC1.1_GND, USBC1.12_GND, USBC1.13_SHELL, USBC1.14_SHELL

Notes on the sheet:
Rev notes: RPDPDM removed; BUZZ1 -> SPK1 (FS-1540) with JPSPK1 (bridged, cut to mute internal speaker); status LED on IO19; IO20 to LED_XOUT via JPXOUT1 (open)
Display bus pull-ups (5.1k to +3V3_SW) for hardware I2C

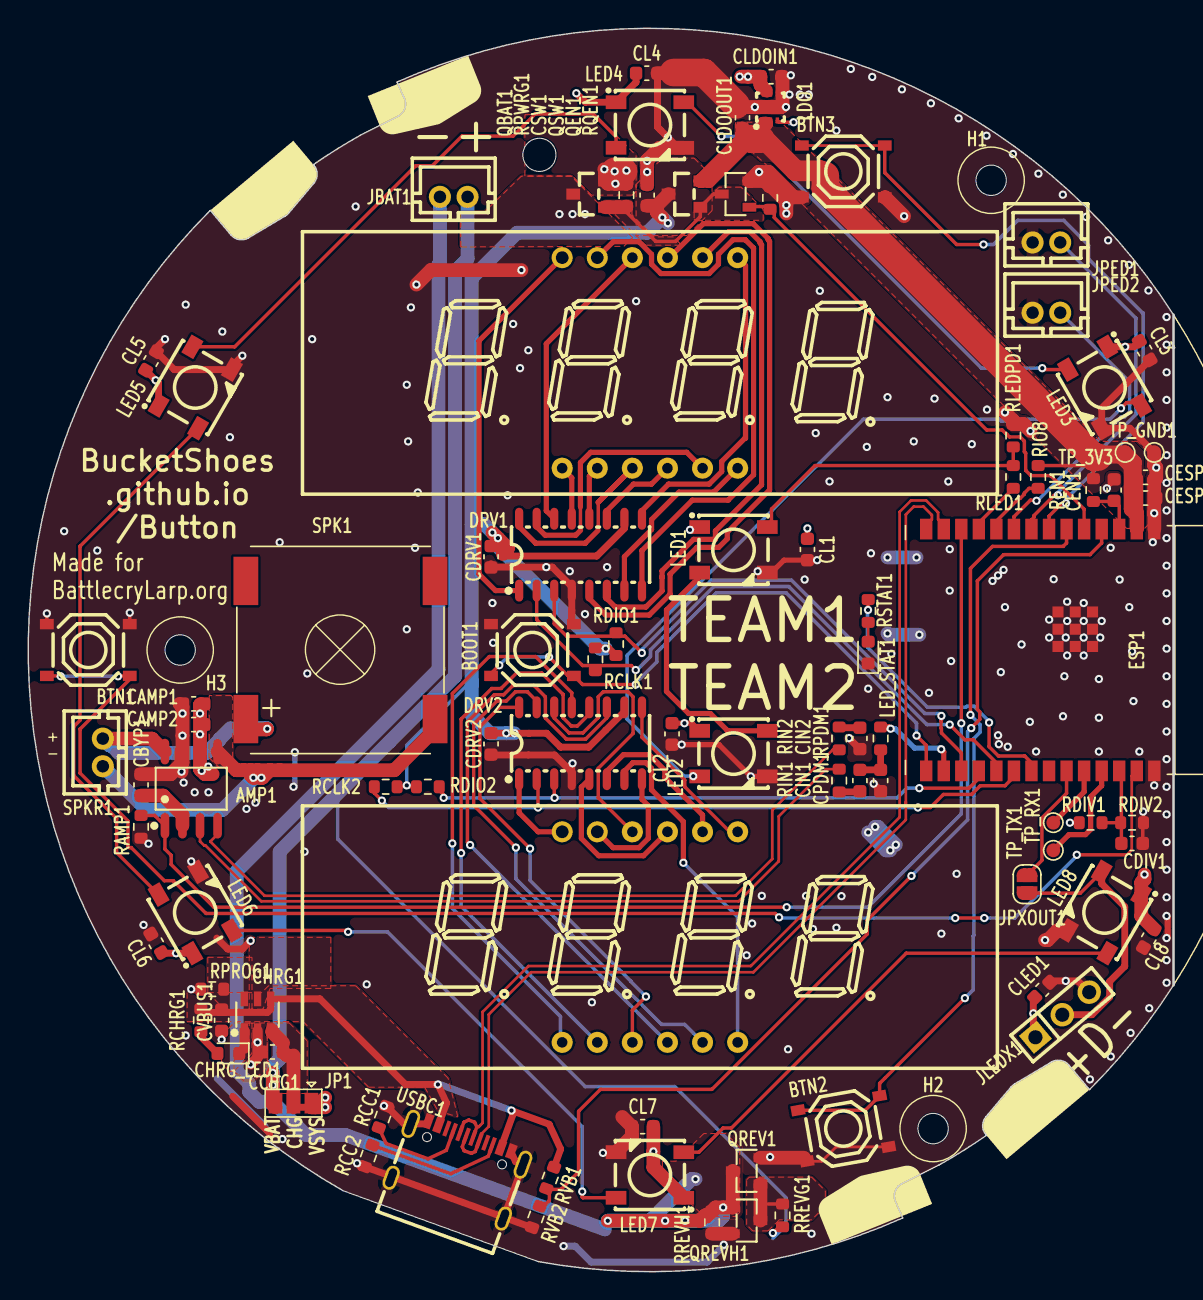
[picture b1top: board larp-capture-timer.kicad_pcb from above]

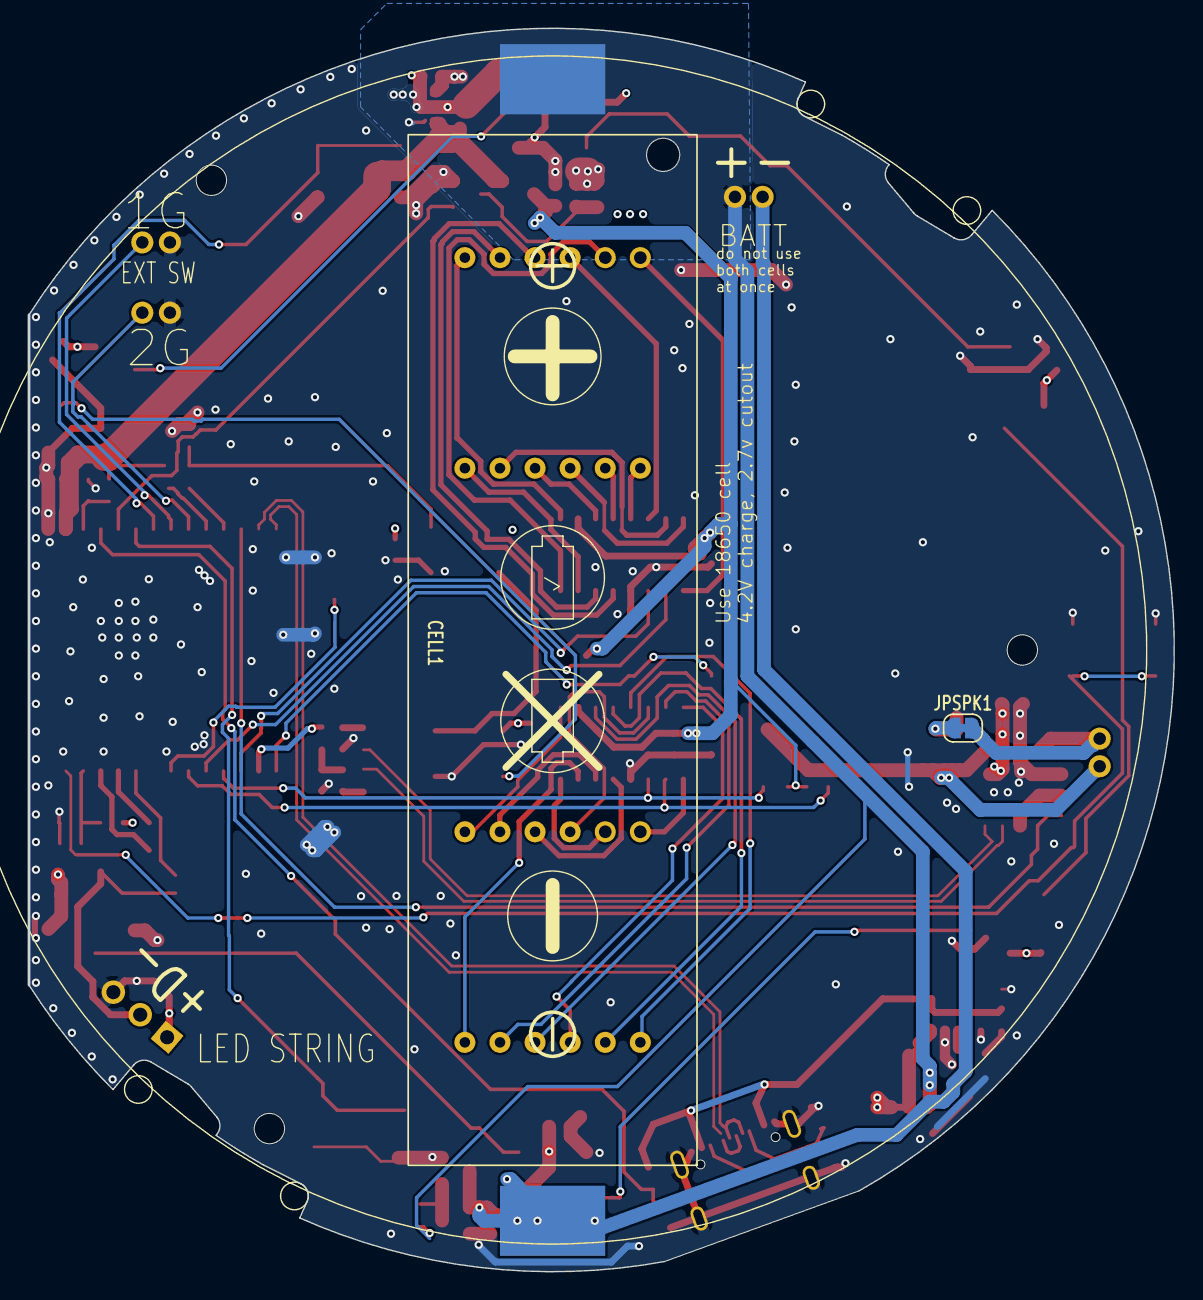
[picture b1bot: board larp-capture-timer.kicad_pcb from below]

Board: 4 copper layers, 82.9 x 90.0 mm, 96 parts (2 on the bottom side), 82 nets.

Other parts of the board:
H1, H2, H3: M2; MountingHole_2.2mm_M2

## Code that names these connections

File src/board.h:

// Pin map for board b43 (see docs/hardware.md).
#pragma once
#include "driver/gpio.h"

#define PIN_PEDAL1      GPIO_NUM_0   // JPED1, contact to GND, no ext pull-up
#define PIN_PEDAL2      GPIO_NUM_1   // JPED2, contact to GND, no ext pull-up
#define PIN_FACE1       GPIO_NUM_2   // BTN1 west, to GND
#define PIN_VSYS_SENSE  GPIO_NUM_3   // ADC1_CH3, VSYS/2 (schematic net "VBAT_SENSE": the divider is on VSYS, after QBAT1)
#define PIN_VBUS_SENSE  GPIO_NUM_4   // ADC1_CH4, 0.6*VBUS
#define PIN_PWR_EN      GPIO_NUM_5   // high = VSYS + 3V3_SW on
#define PIN_FACE2       GPIO_NUM_6   // BTN2 south-east, to GND
#define PIN_FACE3       GPIO_NUM_7   // BTN3 north-east, to GND
#define PIN_BOOT        GPIO_NUM_9   // BOOT1, to GND
#define PIN_LED_DIN     GPIO_NUM_10  // WS2812 chain
#define PIN_AMP_EN      GPIO_NUM_11  // NS4150C CTRL, high = on
#define PIN_PDM         GPIO_NUM_18  // PDM audio out
#define PIN_DISP_DIO1   GPIO_NUM_19
#define PIN_DISP_DIO2   GPIO_NUM_20
#define PIN_DISP_CLK1   GPIO_NUM_21
#define PIN_DISP_CLK2   GPIO_NUM_22
#define PIN_STAT_LED    GPIO_NUM_23  // red, high = on

// WS2812 chain: 0 = LED1 centre (team 1), 1 = LED2 centre (team 2),
// 2..7 = ring LED3..LED8 (NE, N, NW, SW, S, SE: anticlockwise from above),
// 8.. = external strip on JLEDX1.
#define LED_COUNT_BOARD 8
#define LED_COUNT_EXT   16
#define LED_COUNT       (LED_COUNT_BOARD + LED_COUNT_EXT)
#define LED_IDX_TEAM1   0
#define LED_IDX_TEAM2   1
#define LED_IDX_EXT     8
